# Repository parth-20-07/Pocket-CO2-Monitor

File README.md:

# Pocket Carbondioxide Monitor

## Features of our AQI Monitor
- Shows the value of carbondioxide level along with Temperature and Humidity.
- Approx. 1.5 hours Battery Backup.
- MicroUSB Type B charging support.

<br>

## How to assemble the project
1. Download the latest version of firmware from the /Firmware folder
2. Edit the Firmware as per the requirement with the help of guide provided in /Firmware/README.md
3. Order the components from the Bill of Materials as per the requirement.
4. Make the Hardware circuit
   1.  Solder them on General Purpose PCB Board using the design below (or)
   2.  Order the PCB by providing the PCB Developer with the gerber file available in /Hardware/PCB_Gerber.zip and solder all the component on it
5.  Upload the firmware on the the hardware

<br>

## How to use the device
1. Press the push button to turn on the device.
2. The device will start with a bootup screen with the company logo.
3. The landing page will show the value of Carbondioxide, Temperature, Humidity of screen.

<center>

## Schematic Design

<br><br>

## PCB Design

Top View

Bottom View

## Rendered Images

</center>

## Tools Used

<br><br>

## Design Details
- Designed for: Ecologic Pvt. Ltd.
- Designed by: [Parth Patel](mailto:parth.pmech@gmail.com)

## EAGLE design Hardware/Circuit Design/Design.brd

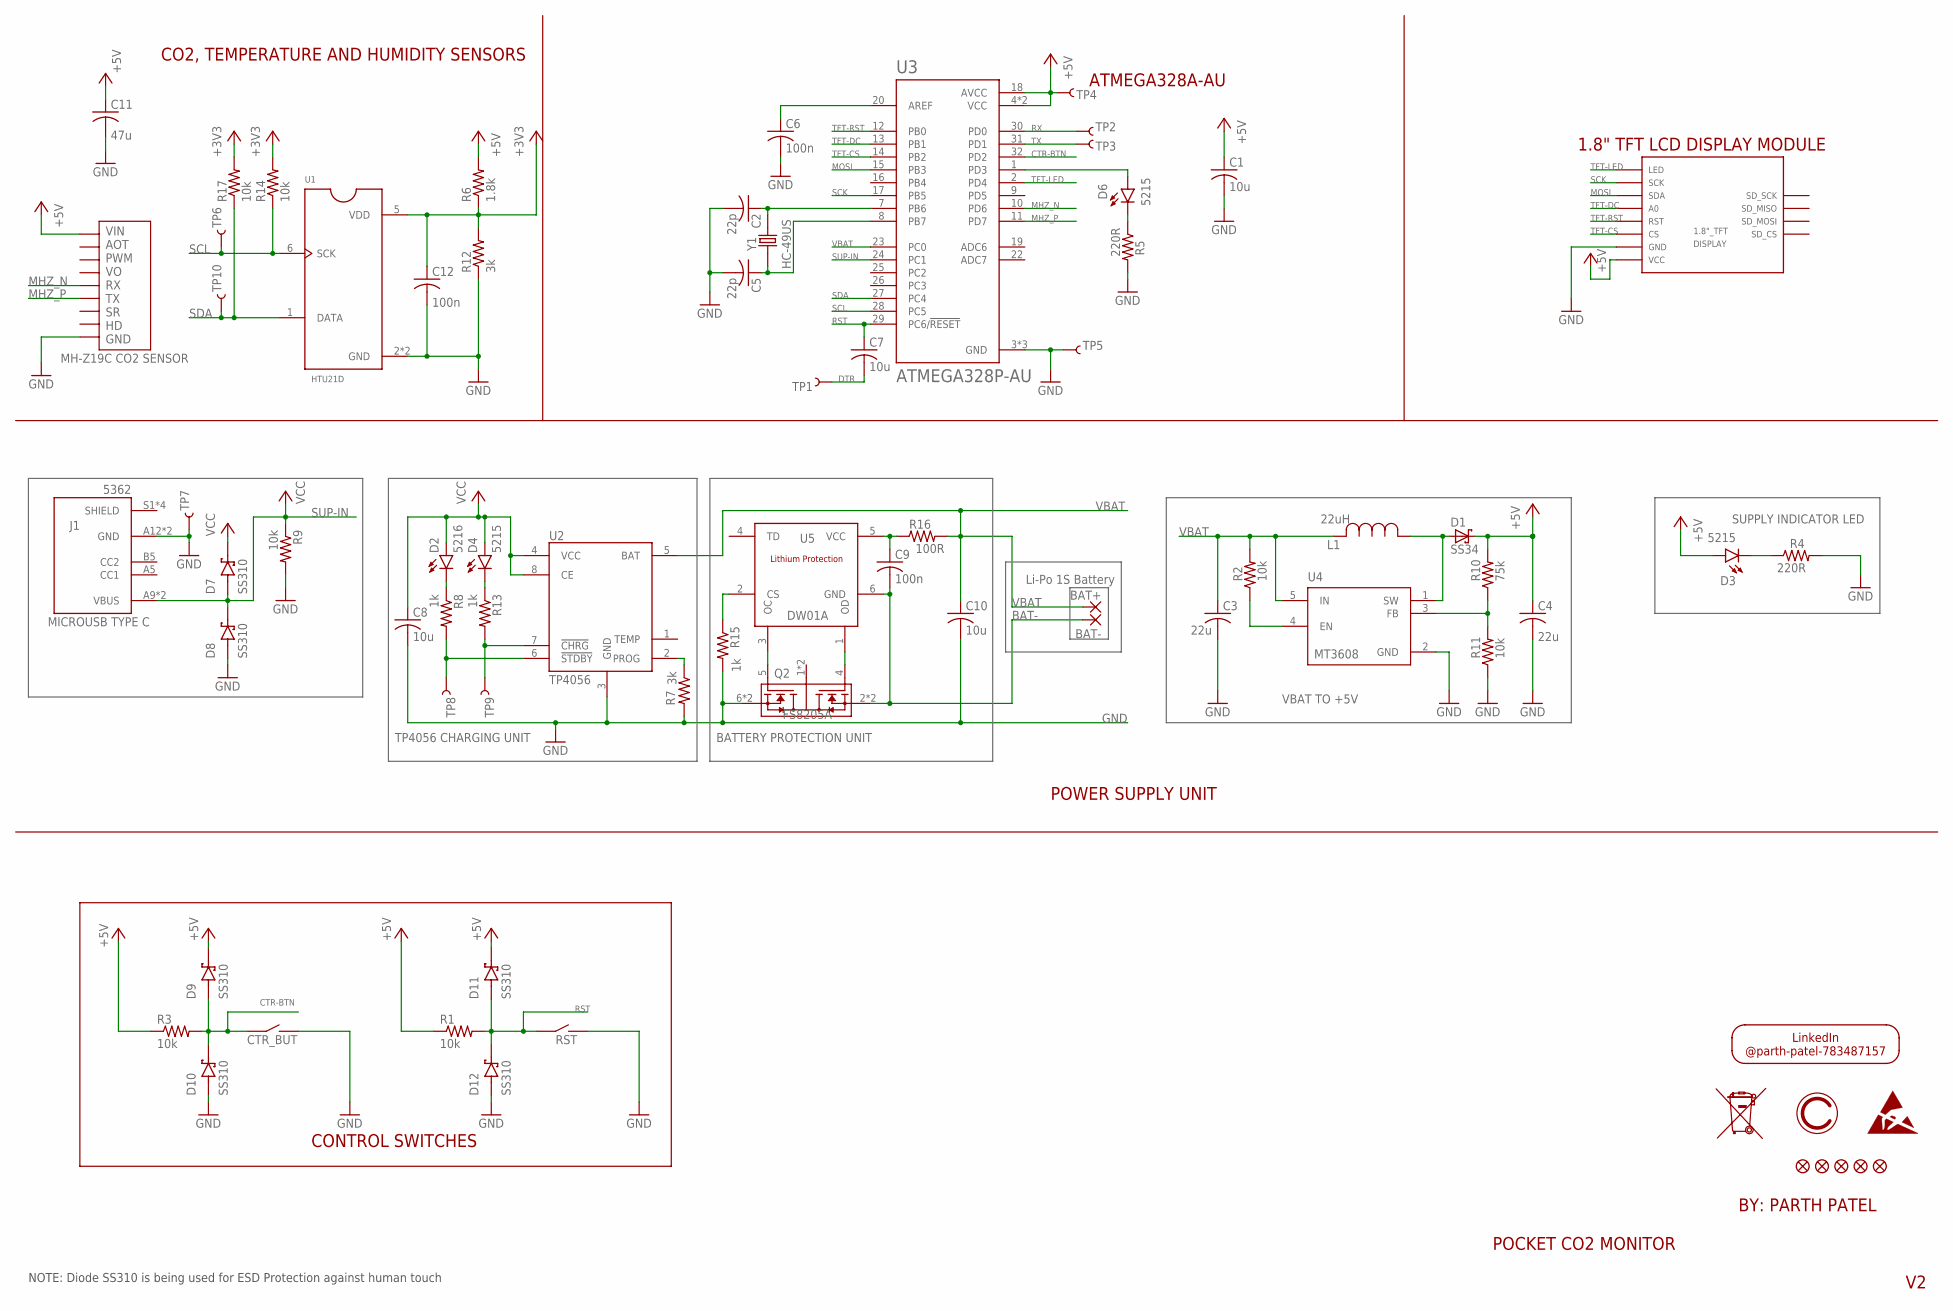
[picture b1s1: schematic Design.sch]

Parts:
BAT+: WIREPADSMD5-2,5; 5-2,5
BAT-: WIREPADSMD5-2,5; 5-2,5
C1, C7, C8, C10: 10u; C0805
C2, C5: 22p; C0805
C3, C4: 22u; C0805
C6, C9, C12: 100n; C0805
C11: 47u; C0805
CTR_BUT: 7058; DIP_3X6MM_SIDE_PRESS_2PIN
D1: SS34; DO214
D2: 5216; CHIP-LED0603
D3, D4, D6: 5215; CHIP-LED0603
D7, D8, D9, D10, D11, D12: SS310; DIOM6859X262N
DISPLAY: 1.8"_TFT
FID1, FID2, FID3, FID4, FID5: FIDUCIAL""; FIDUCIAL_1MM
J1: 5362; GCT_USB4125-GF-A-0190_REVA2
L1: 22uH; INDM125125X800N
Q2: FS8205A; SOP65P640X120-8N
R1, R2, R3, R9, R11, R14, R17: 10k; R0805
R4, R5: 220R; R0805
R6: 1.8k; R0805
R7, R12: 3k; R0805
R8, R13, R15: 1k; R0805
R10: 75k; R0805
R16: 100R; R0805
RST: 7058; DIP_3X6MM_SIDE_PRESS_2PIN
TP1, TP2, TP3, TP4, TP5, TP6, TP7, TP10: TEST-POINT3; PAD.03X.03
TP8: ~STDBY; PAD.03X.03
TP9: ~CHRG; PAD.03X.03
U1: HTU21D; QFN100P300X300X100-7N
U2: TP4056; SOP127P600X175-9N
U3: ATMEGA328P-AU; QFP80P900X900X120-32N
U4: MT3608; SOT95P280X145-6N
U5: DW01A; SOT23-6
U$1: LOGO_17MM; FOOTPRINT_17MM
U$2: MH-Z19C
Y1: HC-49US; XTAL_ECS-160-20-4X

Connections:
+3V3: C12.1, R6.1, R12.2, R14.2, R17.2, U1.5 (VDD)
+5V: C1.1, C4.1, C11.1, D1.C, D3.A, D9.C (K), D11.C (K), DISPLAY.VCC (+5V), R1.1, R3.1, R6.2, R10.2, TP4.P$1, U3.4 (VCC), U3.6 (VCC), U3.18 (AVCC), U$2.VIN
BAT-: BAT-.1, C9.2, Q2.2 (S1), Q2.3 (S1), U5.6 (GND)
CTR-BTN: CTR_BUT.P$1 (S1), D9.A, D10.C (K), R3.2, U3.32 (PD2)
DTR: C7.2, TP1.P$1
GND: C1.2, C2.2, C3.2, C4.2, C5.2, C6.2, C8.2, C10.2, C11.2, C12.2, CTR_BUT.P$2 (S2), D8.A, D10.A, D12.A, DISPLAY.GND, J1.A12 (GND), J1.B12 (GND), Q2.6 (S2), Q2.7 (S2), R4.2, R5.2, R7.2, R9.2, R11.1, R12.1, R15.2, RST.P$2 (S2), TP5.P$1, TP7.P$1, U1.2 (GND), U1.PAD (GND), U2.3 (GND), U3.3 (GND), U3.5 (GND), U3.21 (GND), U4.2 (GND), U$2.GND
MHZ_N: U3.10 (PD6), U$2.RX
MHZ_P: U3.11 (PD7), U$2.TX
MOSI: DISPLAY.SDA, U3.15 (PB3)
unnamed: C5.1, U3.8 (PB7), Y1.1
unnamed: D3.C, R4.1
unnamed: R2.1, U4.4 (EN)
unnamed: C6.1, U3.20 (AREF)
unnamed: D4.C, R13.1
unnamed: D2.C, R8.1
unnamed: C2.1, U3.7 (PB6), Y1.2
unnamed: D1.A, L1.1, U4.1 (SW)
unnamed: R10.1, R11.2, U4.3 (FB)
unnamed: D6.C, R5.1
unnamed: D6.A, U3.1 (PD3)
unnamed: Q2.5 (G2), U5.3 (OC)
unnamed: R13.2, TP9.P$1, U2.7 (!CHRG)
unnamed: R8.2, TP8.P$1, U2.6 (!STDBY)
unnamed: R7.1, U2.2 (PROG)
unnamed: Q2.4 (G1), U5.1 (OD)
unnamed: R15.1, U5.2 (CS)
unnamed: C9.1, R16.1, U5.5 (VCC)
RST: C7.1, D11.A, D12.C (K), R1.2, RST.P$1 (S1), U3.29 (PC6/!RESET)
RX: TP2.P$1, U3.30 (PD0)
SCK: DISPLAY.SCK, U3.17 (PB5)
SCL: R14.1, TP6.P$1, U1.6 (SCK), U3.28 (PC5)
SDA: R17.1, TP10.P$1, U1.1 (DATA), U3.27 (PC4)
SUP-IN: D7.A, D8.C (K), J1.A9 (VBUS), J1.B9 (VBUS), R9.1, U3.24 (PC1)
TFT-CS: DISPLAY.CS, U3.14 (PB2)
TFT-DC: DISPLAY.DC (A0), U3.13 (PB1)
TFT-LED: DISPLAY.LED, U3.2 (PD4)
TFT-RST: DISPLAY.RST, U3.12 (PB0)
TX: TP3.P$1, U3.31 (PD1)
VBAT: BAT+.1, C3.1, C10.1, L1.2, R2.2, R16.2, U2.5 (BAT), U3.23 (PC0), U4.5 (IN)
VCC: C8.1, D2.A, D4.A, D7.C (K), U2.4 (VCC), U2.8 (CE)

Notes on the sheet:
POWER SUPPLY UNIT
POCKET CO2 MONITOR
BY: PARTH PATEL
CONTROL SWITCHES
ATMEGA328A-AU
1.8" TFT LCD DISPLAY MODULE
MICROUSB TYPE C
VBAT TO +5V
TP4056 CHARGING UNIT
Li-Po 1S Battery
BATTERY PROTECTION UNIT
SUPPLY INDICATOR LED
NOTE: Diode SS310 is being used for ESD Protection against human touch
CO2, TEMPERATURE AND HUMIDITY SENSORS

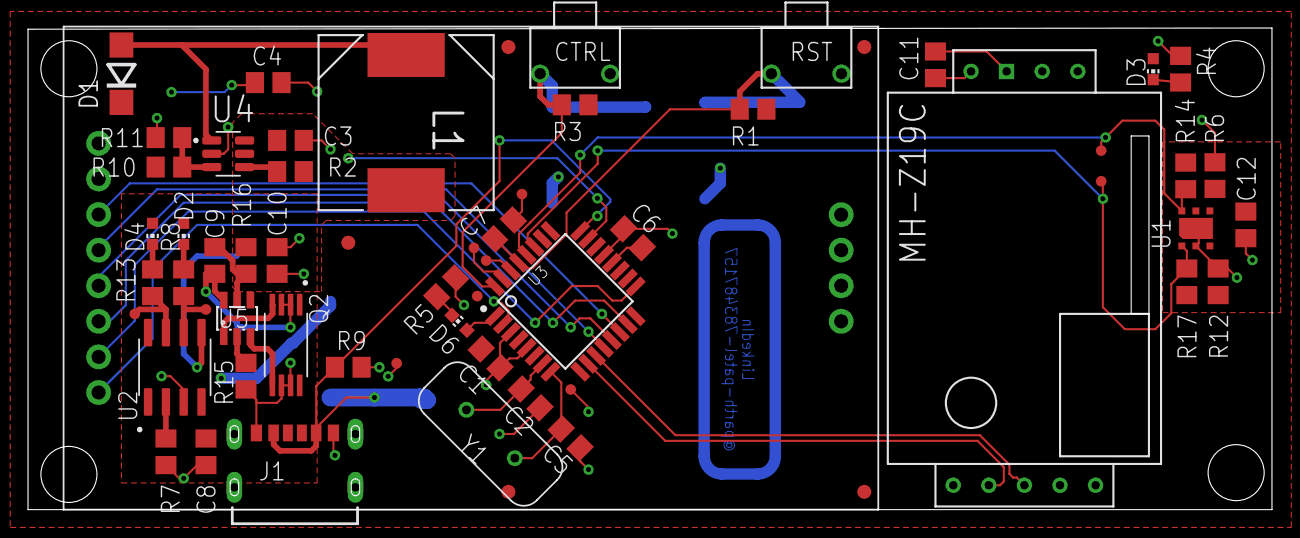
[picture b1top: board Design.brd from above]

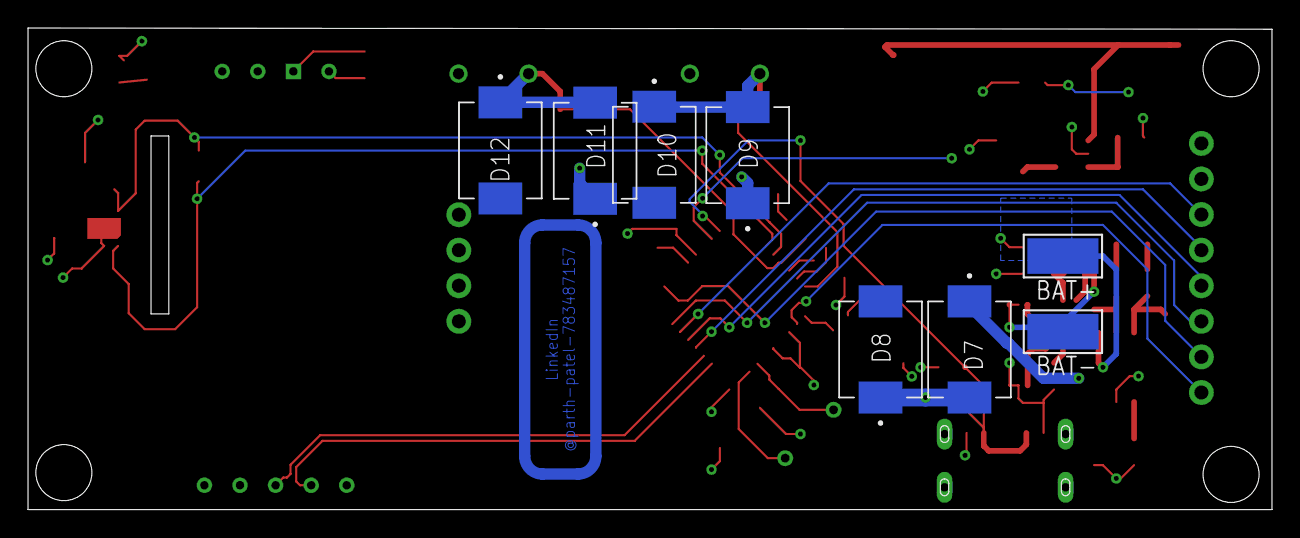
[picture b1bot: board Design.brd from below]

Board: 2 copper layers, 88.8 x 34.4 mm, 71 parts (9 on the bottom side), 40 nets.

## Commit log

2022-03-10 Add the Circuit Schematic and PCB design
2022-04-05 Design display for co2 monitor
2022-04-06 Complete the primary testing of the co2 monitor. Battery Visual still pending
2022-04-26 Correct the sleep mode enter function and add the new board design
2022-06-20 Add the product sketch for the monitor
2022-06-24 Correct the charging logo, data update frequency and graph first plotting time
2022-06-25 Add Circuit CAD Model
2022-07-12 Change Mounting Holes size from M1.5 to M4
2022-07-12 Change the screen order as the boot screen shows up everytime screen changes from graph screen to graphic screen
2022-07-12 Add the CAD model of circuit

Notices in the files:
parts and their libraries:
SparkFun-Connectors: Licensing: Creative Commons ShareAlike 4.0 International - https://creativecommons.org/licenses/by-sa/4.0
